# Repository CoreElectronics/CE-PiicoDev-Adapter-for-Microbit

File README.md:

# PiicoDev® Adapter for Micro:bit

This is the hardware repo for the [PiicoDev® Adapter for Micro:bit](https://core-electronics.com.au/catalog/product/view/sku/CE07688)

Connect your Micro:bit with the outside world using [PiicoDev® Adapter for Micro:bit](https://core-electronics.com.au/catalog/product/view/sku/CE07688). With this adapter you can experiment with sensors from the PiicoDev range giving your Micro:bit new sensing abilities. Use the on-board PiicoDev connectors to quickly and easily connect with the [PiicoDev](https://core-electronics.com.au/piicodev) family of sensor modules without soldering.

- Connect new sensors to your Micro:bit
- No soldering necessary
- Crocodile clip connections are broken out again, so you can still hand wire to your Micro:bit
- PiicoDev connectors, compatible with Qwiic and STEMMA QT (3.3V only)
- Manufactured and [supported](https://core-electronics.com.au/contacts/) in Australia by Core Electronics

# License
This project is open source - please review the LICENSE.md file for further licensing information.

If you have any technical questions, or concerns about licensing, please contact technical support on the [Core Electronics forums](https://forum.core-electronics.com.au/).

---
*\"PiicoDev" is a registered trademark of Core Electronics Pty Ltd*

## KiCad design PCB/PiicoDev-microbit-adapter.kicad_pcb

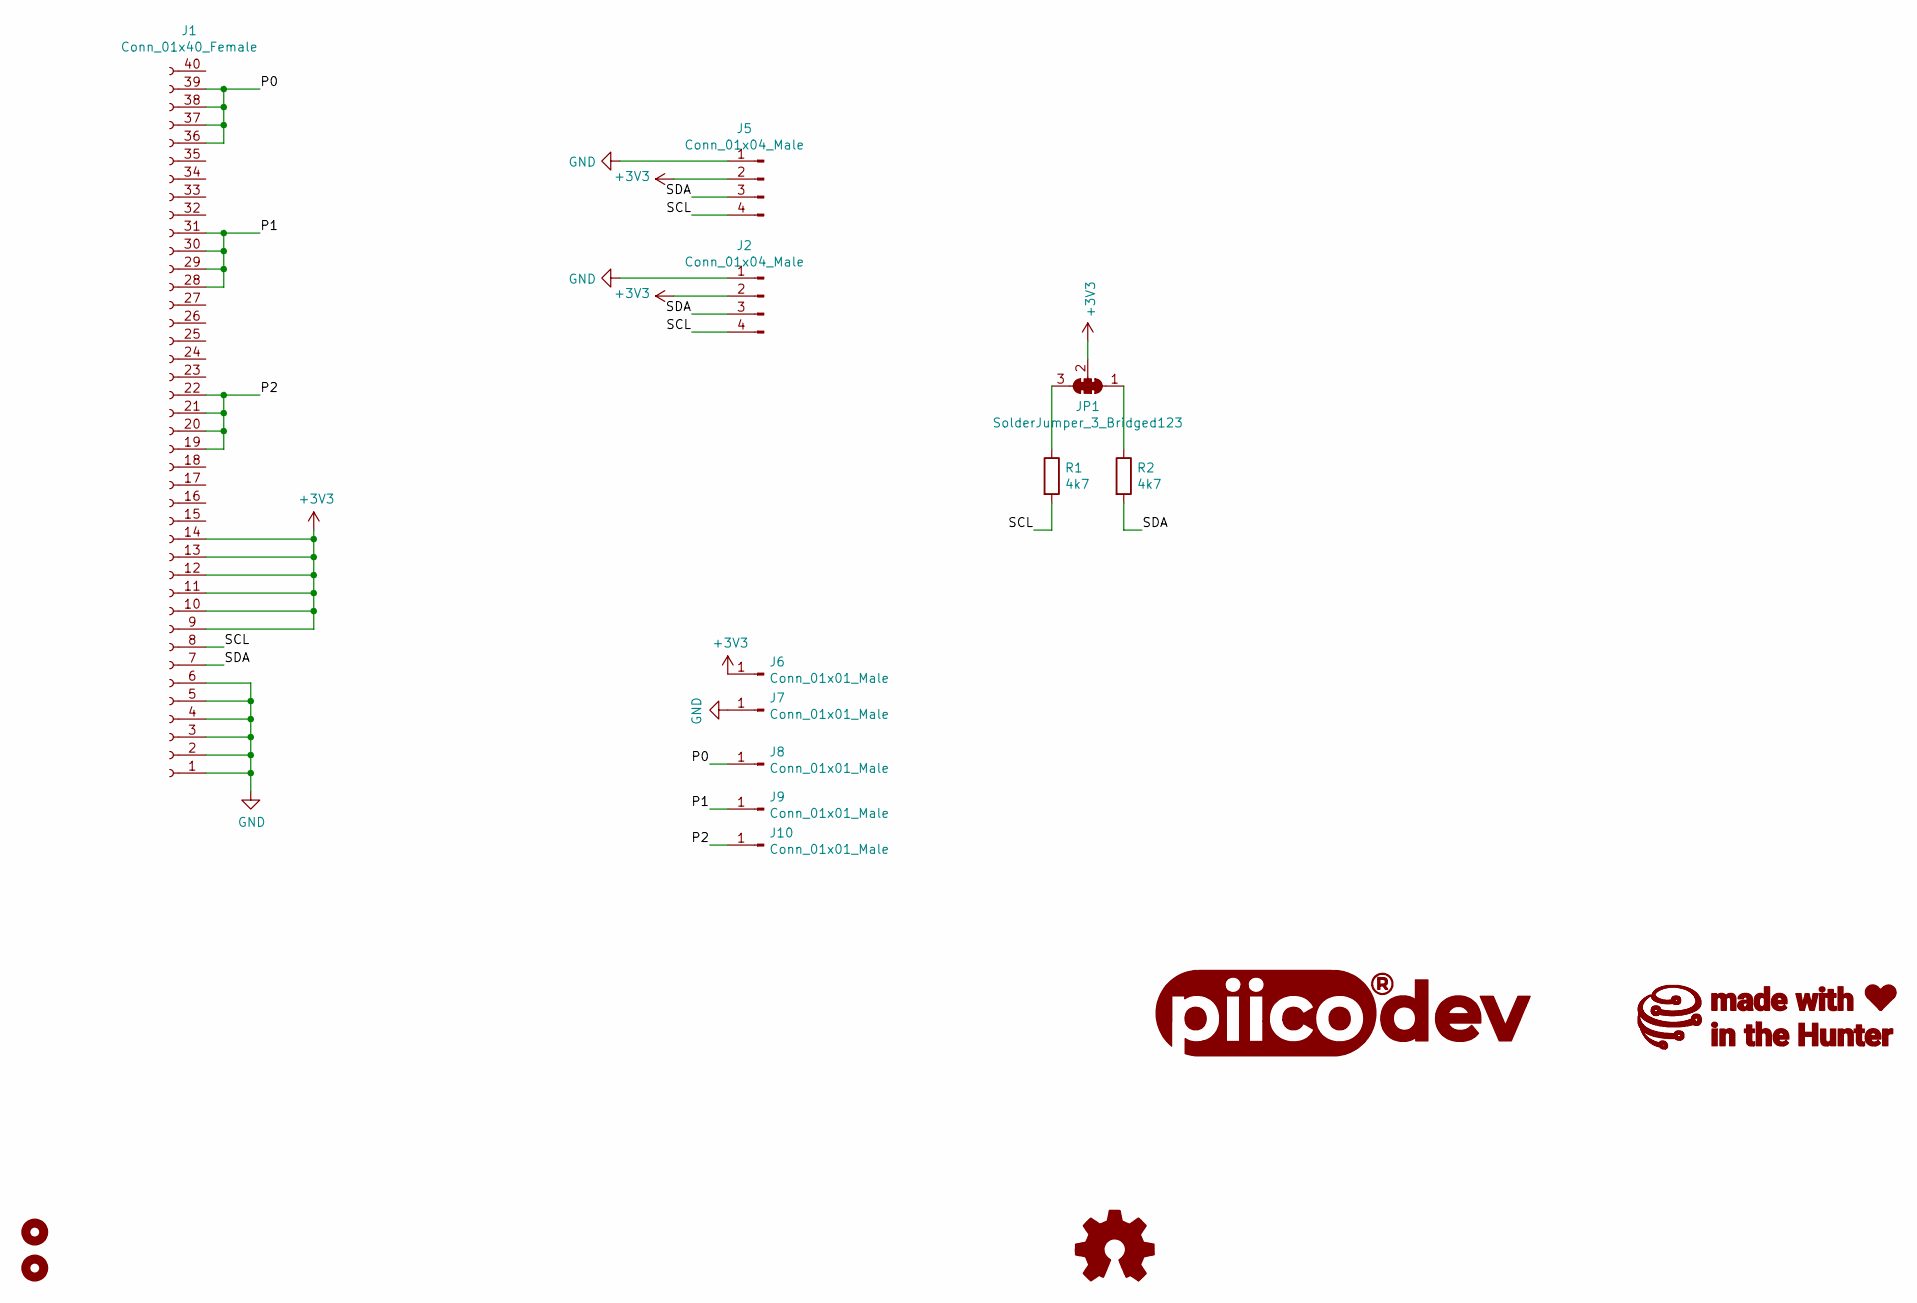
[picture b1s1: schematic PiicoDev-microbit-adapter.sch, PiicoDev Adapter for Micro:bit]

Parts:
G1: LOGO_PiicoDev; piicodev_logo_14.9x3.6mm
G2: LOGO_CoreElectronics_made-with-love; CoreElectronics_logo_5mm_v2
H1, H2: MountingHole_2.7mm_M2.5
J1: Conn_01x40_Female; Conn_microbit_Right_Angle_SMT
J2, J5: Conn_01x04_Male; JST_SH_SM04B-SRSS-TB_1x04-1MP_P1.00mm_Horizontal
J6, J7, J8, J9, J10: Conn_01x01_Male; Conn_microbit_clip
JP1: SolderJumper_3_Bridged123; SolderJumper-3_P1.3mm_Closed_RoundedPad1.0x1.5mm
LOGO1: Logo_Open_Hardware_Large; oshw_3.9x3.5mm
R1, R2: 4k7; R_0402_1005Metric

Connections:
+3V3: J1.9, J1.10, J1.11, J1.12, J1.13, J1.14, J2.2, J5.2, J6.1, JP1.2 (C)
/P0: J1.36, J1.37, J1.38, J1.39, J8.1
/P1: J1.28, J1.29, J1.30, J1.31, J9.1
/P2: J1.19, J1.20, J1.21, J1.22, J10.1
/SCL: J1.8, J2.4, J5.4, R1.2
/SDA: J1.7, J2.3, J5.3, R2.2
GND: J1.1, J1.2, J1.3, J1.4, J1.5, J1.6, J2.1, J5.1, J7.1
unnamed: JP1.1 (A), R2.1
unnamed: JP1.3 (B), R1.1

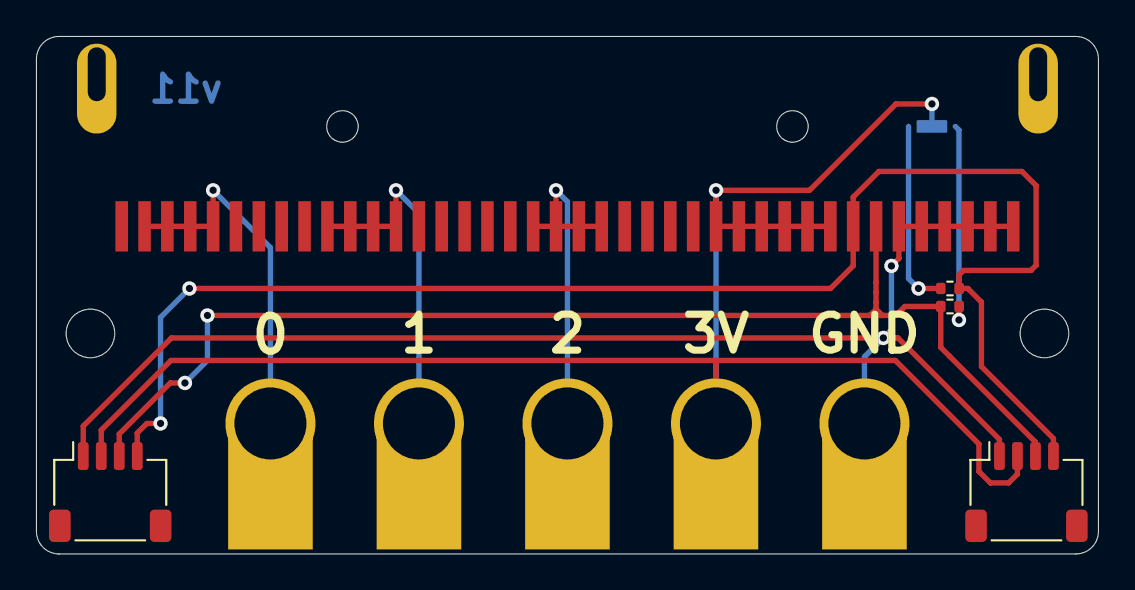
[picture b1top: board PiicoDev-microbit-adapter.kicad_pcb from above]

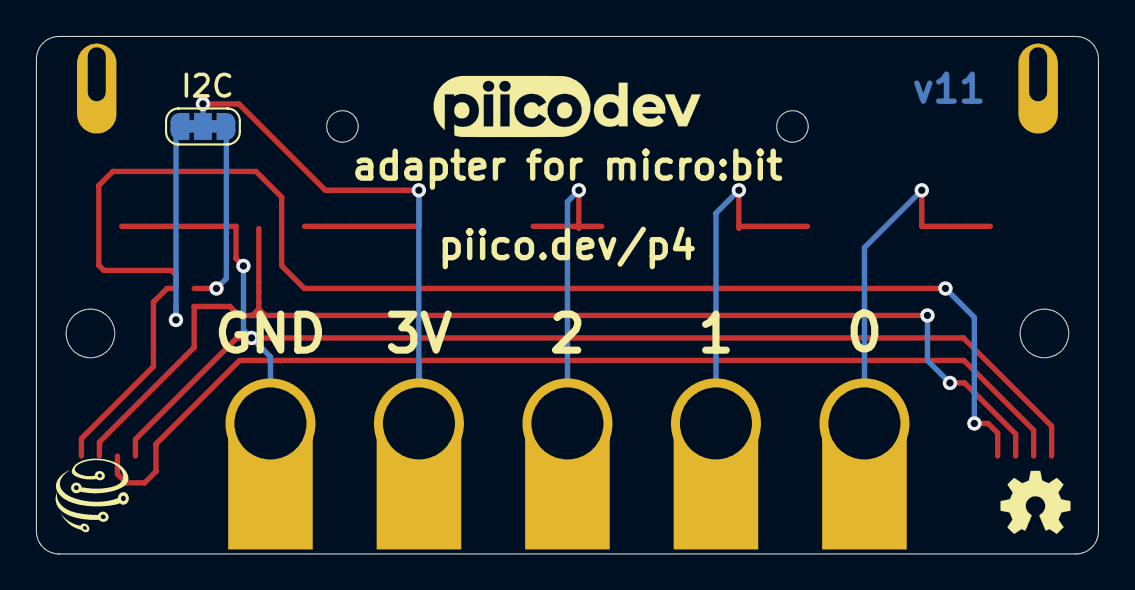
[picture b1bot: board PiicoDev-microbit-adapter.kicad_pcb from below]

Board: 2 copper layers, 59.0 x 28.8 mm, 16 parts (4 on the bottom side), 9 nets.

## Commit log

2021-02-23 v0 with hand-made microbit connector
    This version uses a hand-made microbit connector with dimensions taken from a sample. It is to get a prototype in the pipeline until our supplier returns to us with a datasheet
2021-02-26 v1 with premade microbit connector
2021-03-31 Add Core Logo
2021-03-31 Add License and Readme
2021-03-31 Add schematic pdf
2021-11-01 Update artwork, bump to v11

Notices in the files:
PCB/PiicoDev-microbit-adapter.sch:
Released under  Creative Commons Share-alike 4.0 International
https://creativecommons.org/licenses/by-sa/4.0
